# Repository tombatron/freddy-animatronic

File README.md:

# Freddy Animatronic: custom controller

Reverse-engineering the control board of a Spirit Halloween Freddy Fazbear animatronic, so it can be replaced with an ESP32-S3 that runs custom reactions (and later, sound and AI).

**Status (November 2026):** Phase 1 (listen and decode) is complete. Every motor, sensor and protocol is understood, and the ESP32 already drives both elbows directly. Phase 2 (a custom, drop-in controller board) is under way: the [rev A PCB](docs/phase2-pcb.md) (with a speaker amp) is laid out in KiCad, routed and ready to order, with a 3D-printable enclosure. Modules are in hand, and two bench tests are ready to run: the [power test](docs/phase2-power-test.md) and the [head test](docs/head-bench-test.md).

| Part | What it is | Status |
| --- | --- | --- |
| Shoulders | Reversing DC motor (~2 Ω) + one position switch | Decoded, both arms |
| Elbows | Smart serial servo module, 9600 baud, custom frames | Decoded **and controlled** by the ESP32 |
| Eyes | Sweep motor (cam disc), home switch, LEDs | Decoded; LED and motor currents measured |
| Trigger | 3.5mm jack, contact closure | Confirmed |
| PIR motion sensor | 3-wire sensor | Measured: yellow = ~7V power, orange = signal (~1.3V on motion) |

## System overview

```mermaid
flowchart LR
    PSU["7.2V 4A adapter"] --> PB["Power breakout<br/>5A fuse + GND tap"]
    PB --> SB["Stock board SD03-122<br/>(FMD FT60E122 MCU)"]
    SB -- "cable 1: H-bridge" --> SH["Shoulder motors x2"]
    SB -- "cable 3: 3.3V, GND, switch" --> SS["Shoulder switches x2"]
    SB -- "cable 2: 7V, GND, 9600 serial" --> EL["Elbow servo modules x2"]
    SB -- "head 3: switched" --> EM["Eye sweep motor"]
    SB -- "head 1: pull-up" --> EH["Eye home switch"]
    SB -- "head 2: switched" --> LED["Eye LEDs"]
    PIR["PIR sensor"] --> SB
    TRIG["Trigger jack"] --> SB
```

In Phase 2 the stock board is removed and an ESP32-S3 controller plugs into the same connectors.

## Repository layout

| Path | Contents |
| --- | --- |
| [docs/hardware-map.md](docs/hardware-map.md) | Every cable and wire, with its role and measured voltages |
| [docs/arms.md](docs/arms.md) | Shoulder drive, shoulder switch, elbow overview, measured ranges |
| [docs/elbow-protocol.md](docs/elbow-protocol.md) | The elbow serial protocol and checksum, and how it was cracked |
| [docs/head.md](docs/head.md) | Eye motor, home switch and LEDs |
| [docs/phase1-harness.md](docs/phase1-harness.md) | How the listening harness, tap boards and test rigs are built |
| [docs/tooling.md](docs/tooling.md) | Arduino IDE, picocom, PulseView/sigrok setup (Arch Linux and Windows) |
| [docs/troubleshooting.md](docs/troubleshooting.md) | Lessons learned the hard way |
| [docs/phase2-plan.md](docs/phase2-plan.md) | Requirements and parts for the custom controller |
| [docs/head-bench-test.md](docs/head-bench-test.md) | Head bench test: what else can the eyes do (speed, reverse, aim, glances, LED effects)? |
| [docs/phase2-power-test.md](docs/phase2-power-test.md) | Breadboard power test: does the 5V rail survive a shoulder lift? |
| [docs/phase2-pcb.md](docs/phase2-pcb.md) | Controller PCB rev A: KiCad project, GPIO map, connectors, power budget, ordering, enclosure |
| [docs/future-improvements.md](docs/future-improvements.md) | Later upgrades: eye angle sensor (AS5600 on the eye pivot), stock-compatible eye switch replacement, servo-driven eyes + radar tracking |
| [hardware/controller/](hardware/controller/) | KiCad project, fab files for JLCPCB, renders, enclosure, BOM, net list |
| [schematics/](schematics/) | Phase 1 SVG schematics (`tools/make_schematics.py`) and the controller schematic exported from KiCad |
| [firmware/](firmware/) | ESP32-S3 Arduino sketches (loggers, sniffer, elbow controllers) |
| [tools/](tools/) | `elbow_frame.py` (build and check frames), schematic generators, `kicad/` (generates the controller's KiCad project and enclosure from `design.py`) |
| [captures/](captures/) | Raw logs from the stock board, used for the analysis |

## Quick start: move an elbow

1. Build the elbow replay rig ([docs/phase1-harness.md](docs/phase1-harness.md#elbow-replay-rig)), with the stock board disconnected.
2. Flash [`firmware/freddy_elbow_controller`](firmware/freddy_elbow_controller/) to an ESP32-S3.
3. `picocom -b 115200 /dev/ttyACM0`, press `h` to home, then use the arrow keys to jog.

Or build any frame by hand:

```bash
python3 tools/elbow_frame.py build -400 1500
# AB 01 09 41 70 FE DC 05 45
```

## Safety notes

- Every ESP32 input goes through a 47k/22k divider (7.6V becomes 2.4V) or a 1kΩ series resistor. Nothing on the harness is wired straight to a GPIO.
- **Always tie the ESP32's ground to Freddy's ground.** A missing ground caused most of the confusing readings during Phase 1.
- Elbow commands are clamped to the measured ranges (right −700..350, left −700..550).

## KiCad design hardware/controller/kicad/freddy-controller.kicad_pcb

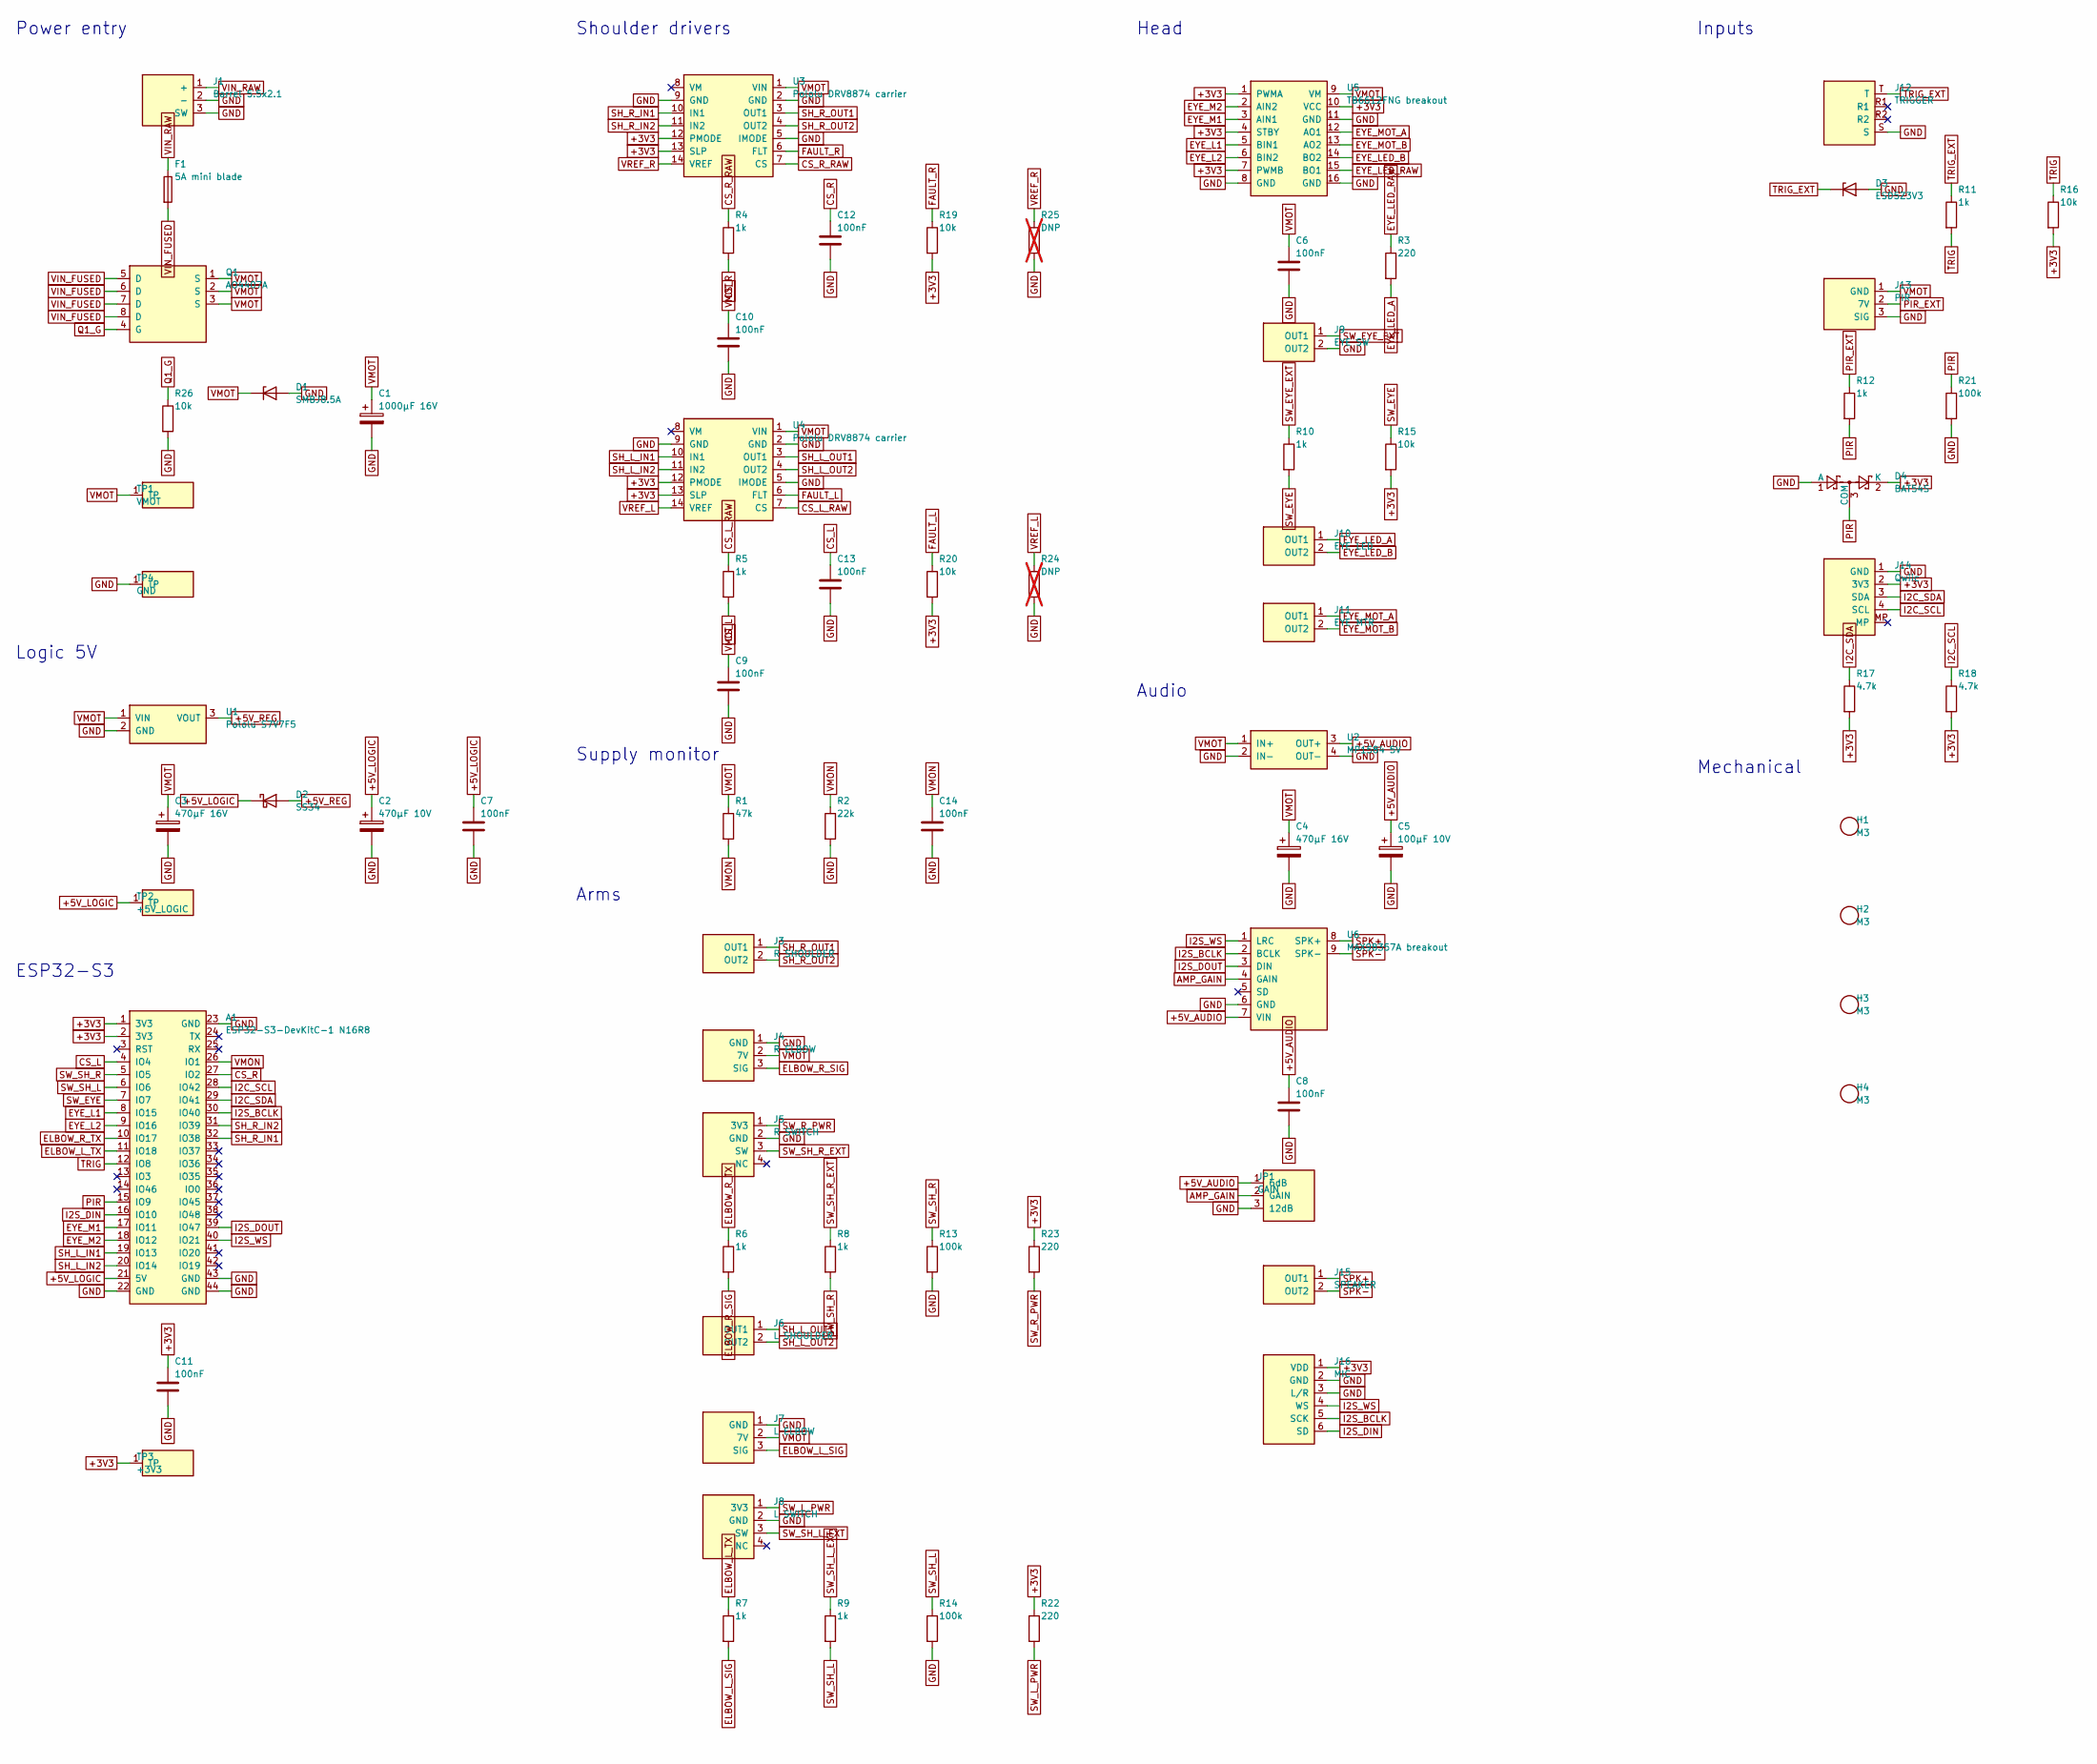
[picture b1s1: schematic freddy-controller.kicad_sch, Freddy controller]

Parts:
A1: ESP32-S3-DevKitC-1 N16R8; ESP32-S3-DevKitC-1_Socket; MPN YD-ESP32-S3 / DevKitC-1 (in hand)
C1: 1000µF 16V; CP_Radial_D10.0mm_P5.00mm; MPN 1000µF 16V low-ESR, 10mm
C2: 470µF 10V; CP_Radial_D6.3mm_P2.50mm; MPN 470µF 10V, 6.3mm
C3, C4: 470µF 16V; CP_Radial_D8.0mm_P3.50mm; MPN 470µF 16V, 8mm
C5: 100µF 10V; CP_Radial_D5.0mm_P2.00mm; MPN 100µF 10V, 5mm
C6, C7, C8, C9, C10, C11, C12, C13, C14: 100nF; C_0805_2012Metric
D1: SMBJ8.5A; D_SMB; MPN SMBJ8.5A (unidirectional TVS)
D2: SS34; D_SMA; MPN SS34
D3: ESD5Z3V3; D_SOD-523; MPN ESD5Z3V3
D4: BAT54S; SOT-23; MPN BAT54S
F1: 5A mini blade; Fuseholder_Blade_Mini_Keystone_3568; MPN Keystone 3568 + 5A mini blade fuse
H1, H2, H3, H4: M3; MountingHole_3.2mm_M3
J1: Barrel 5.5x2.1; BarrelJack_Horizontal; MPN 5.5x2.1mm PCB barrel jack, 5A+, CUI PJ-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
J3: R SHOULDER; Pigtail_1x2_P2.54mm_ZipTie; MPN JST SM 2-pin pigtail (in hand)
J4: R ELBOW; Pigtail_1x3_P2.54mm_ZipTie; MPN JST SM 3-pin pigtail (in hand)
J5: R SWITCH; Pigtail_1x4_P2.54mm_ZipTie; MPN JST SM 4-pin pigtail (in hand)
J6: L SHOULDER; Pigtail_1x2_P2.54mm_ZipTie; MPN JST SM 2-pin pigtail (in hand)
J7: L ELBOW; Pigtail_1x3_P2.54mm_ZipTie; MPN JST SM 3-pin pigtail (in hand)
J8: L SWITCH; Pigtail_1x4_P2.54mm_ZipTie; MPN JST SM 4-pin pigtail (in hand)
J9: EYE SW; Pigtail_1x2_P2.54mm_ZipTie; MPN JST SM 2-pin pigtail (in hand)
J10: EYE LED; Pigtail_1x2_P2.54mm_ZipTie; MPN JST SM 2-pin pigtail (in hand)
J11: EYE MTR; Pigtail_1x2_P2.54mm_ZipTie; MPN JST SM 2-pin pigtail (in hand)
J12: TRIGGER; Jack_3.5mm_KoreanHropartsElec_PJ-320D-4A_Horizontal; MPN PJ-320D 3.5mm jack
J13: PIR; Pigtail_1x3_P2.54mm_ZipTie; MPN JST SM 3-pin pigtail (in hand)
J14: Qwiic; JST_SH_SM04B-SRSS-TB_1x04-1MP_P1.00mm_Horizontal; MPN JST SM04B-SRSS-TB
J15: SPEAKER; Pigtail_1x2_P2.54mm_ZipTie; MPN solder pads: speaker wires straight in
J16: MIC; PinSocket_1x06_P2.54mm_Vertical; MPN 1x6 female header (INMP441, later)
JP1: GAIN; PinHeader_1x03_P2.54mm_Vertical; MPN 1x3 pin header + jumper
Q1: AO4407A; SOIC-8_3.9x4.9mm_P1.27mm; MPN AO4407A
R1: 47k; R_0805_2012Metric
R2: 22k; R_0805_2012Metric
R3: 220; R_1206_3216Metric
R4, R5, R6, R7, R8, R9, R10, R11, R12: 1k; R_0805_2012Metric
R13, R14, R21: 100k; R_0805_2012Metric
R15, R16, R19, R20, R26: 10k; R_0805_2012Metric
R17, R18: 4.7k; R_0805_2012Metric
R22, R23: 220; R_0805_2012Metric
R24, R25: DNP; R_0805_2012Metric; not fitted
TP1: VMOT; TestPoint_Pad_D1.5mm
TP2: +5V_LOGIC; TestPoint_Pad_D1.5mm
TP3: +3V3; TestPoint_Pad_D1.5mm
TP4: GND; TestPoint_Pad_D1.5mm
U1: Pololu S7V7F5; Pololu_S7V7F5_Upright; MPN Pololu #2119 (in hand)
U2: MP1584 5V; MP1584_Module; MPN MP1584EN fixed 5V module (in hand)
U3, U4: Pololu DRV8874 carrier; Pololu_DRV8874_Carrier_Socket; MPN Pololu #4035 (in hand)
U5: TB6612FNG breakout; TB6612FNG_Clone_ChipUp_Socket; MPN red TB6612FNG clone, labels on bottom, 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
U6: MAX98357A breakout; MAX98357A_Breakout_Socket; MPN Adafruit-style MAX98357A (in hand)

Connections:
+3V3: A1.1 (3V3), A1.2 (3V3), C11.1, D4.2 (K), J14.2 (3V3), J16.1 (VDD), R15.2, R16.2, R17.2, R18.2, R19.2, R20.2, R22.1, R23.1, TP3.1, U3.12 (PMODE), U3.13 (SLP), U4.12 (PMODE), U4.13 (SLP), U5.1 (PWMA), U5.4 (STBY), U5.7 (PWMB), U5.10 (VCC)
+5V_AUDIO: C5.1, C8.1, JP1.1 (6dB), U2.3 (OUT+), U6.7 (VIN)
+5V_LOGIC: A1.21 (5V), C2.1, C7.1, D2.1 (K), TP2.1
+5V_REG: D2.2 (A), U1.3 (VOUT)
AMP_GAIN: JP1.2 (GAIN), U6.4 (GAIN)
CS_L: A1.4 (IO4), C13.1, R5.2
CS_L_RAW: R5.1, U4.7 (CS)
CS_R: A1.27 (IO2), C12.1, R4.2
CS_R_RAW: R4.1, U3.7 (CS)
ELBOW_L_SIG: J7.3 (SIG), R7.2
ELBOW_L_TX: A1.11 (IO18), R7.1
ELBOW_R_SIG: J4.3 (SIG), R6.2
ELBOW_R_TX: A1.10 (IO17), R6.1
EYE_L1: A1.8 (IO15), U5.5 (BIN1)
EYE_L2: A1.9 (IO16), U5.6 (BIN2)
EYE_LED_A: J10.1 (OUT1), R3.2
EYE_LED_B: J10.2 (OUT2), U5.14 (BO2)
EYE_LED_RAW: R3.1, U5.15 (BO1)
EYE_M1: A1.17 (IO11), U5.3 (AIN1)
EYE_M2: A1.18 (IO12), U5.2 (AIN2)
EYE_MOT_A: J11.1 (OUT1), U5.12 (AO1)
EYE_MOT_B: J11.2 (OUT2), U5.13 (AO2)
FAULT_L: R20.1, U4.6 (FLT)
FAULT_R: R19.1, U3.6 (FLT)
GND: A1.22 (GND), A1.23 (GND), A1.43 (GND), A1.44 (GND), C1.2, C2.2, C3.2, C4.2, C5.2, C6.2, C7.2, C8.2, C9.2, C10.2, C11.2, C12.2, C13.2, C14.2, D1.2 (A), D3.2 (A), D4.1 (A), J1.2 (-), J1.3 (SW), J4.1 (GND), J5.2 (GND), J7.1 (GND), J8.2 (GND), J9.2 (OUT2), J12.S, J13.3 (SIG), J14.1 (GND), J16.2 (GND), J16.3 (L/R), JP1.3 (12dB), R2.2, R13.2, R14.2, R21.2, R24.2, R25.2, R26.2, TP4.1, U1.2 (GND), U2.2 (IN-), U2.4 (OUT-), U3.2 (GND), U3.5 (IMODE), U3.9 (GND), U4.2 (GND), U4.5 (IMODE), U4.9 (GND), U5.8 (GND), U5.11 (GND), U5.16 (GND), U6.6 (GND)
I2C_SCL: A1.28 (IO42), J14.4 (SCL), R18.1
I2C_SDA: A1.29 (IO41), J14.3 (SDA), R17.1
I2S_BCLK: A1.30 (IO40), J16.5 (SCK), U6.2 (BCLK)
I2S_DIN: A1.16 (IO10), J16.6 (SD)
I2S_DOUT: A1.39 (IO47), U6.3 (DIN)
I2S_WS: A1.40 (IO21), J16.4 (WS), U6.1 (LRC)
PIR: A1.15 (IO9), D4.3 (COM), R12.2, R21.1
PIR_EXT: J13.2 (7V), R12.1
Q1_G: Q1.4 (G), R26.1
SH_L_IN1: A1.19 (IO13), U4.10 (IN1)
SH_L_IN2: A1.20 (IO14), U4.11 (IN2)
SH_L_OUT1: J6.1 (OUT1), U4.3 (OUT1)
SH_L_OUT2: J6.2 (OUT2), U4.4 (OUT2)
SH_R_IN1: A1.32 (IO38), U3.10 (IN1)
SH_R_IN2: A1.31 (IO39), U3.11 (IN2)
SH_R_OUT1: J3.1 (OUT1), U3.3 (OUT1)
SH_R_OUT2: J3.2 (OUT2), U3.4 (OUT2)
SPK+: J15.1 (OUT1), U6.8 (SPK+)
SPK-: J15.2 (OUT2), U6.9 (SPK-)
SW_EYE: A1.7 (IO7), R10.2, R15.1
SW_EYE_EXT: J9.1 (OUT1), R10.1
SW_L_PWR: J8.1 (3V3), R22.2
SW_R_PWR: J5.1 (3V3), R23.2
SW_SH_L: A1.6 (IO6), R9.2, R14.1
SW_SH_L_EXT: J8.3 (SW), R9.1
SW_SH_R: A1.5 (IO5), R8.2, R13.1
SW_SH_R_EXT: J5.3 (SW), R8.1
TRIG: A1.12 (IO8), R11.2, R16.1
TRIG_EXT: D3.1 (K), J12.T, R11.1
VIN_FUSED: F1.2, Q1.5 (D), Q1.6 (D), Q1.7 (D), Q1.8 (D)
VIN_RAW: F1.1, J1.1 (+)
VMON: A1.26 (IO1), C14.1, R1.2, R2.1
VMOT: C1.1, C3.1, C4.1, C6.1, C9.1, C10.1, D1.1 (K), J4.2 (7V), J7.2 (7V), J13.1 (GND), Q1.1 (S), Q1.2 (S), Q1.3 (S), R1.1, TP1.1, U1.1 (VIN), U2.1 (IN+), U3.1 (VIN), U4.1 (VIN), U5.9 (VM)
VREF_L: R24.1, U4.14 (VREF)
VREF_R: R25.1, U3.14 (VREF)

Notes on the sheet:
Power entry
Logic 5V
ESP32-S3
Shoulder drivers
Supply monitor
Arms
Head
Audio
Inputs
Mechanical

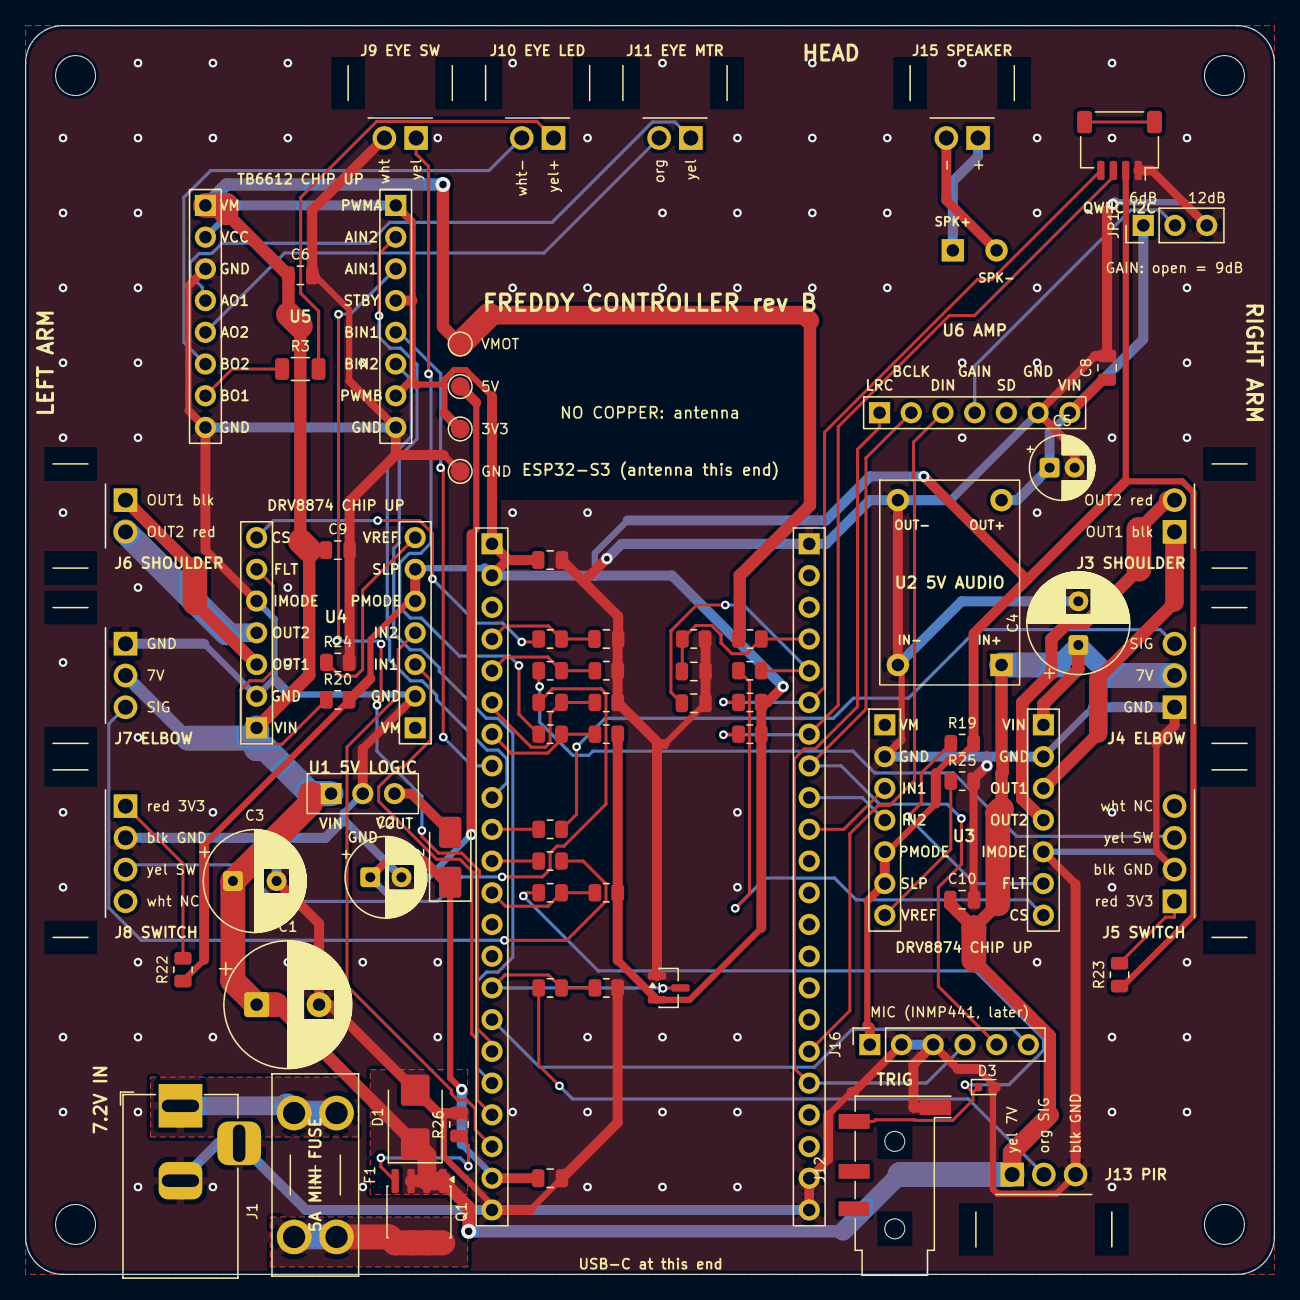
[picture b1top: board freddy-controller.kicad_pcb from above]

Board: 2 copper layers, 100.0 x 100.0 mm, 77 parts (0 on the bottom side), 60 nets.

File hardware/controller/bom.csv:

Refs,Qty,Value,Part / MPN,Footprint,Fitting
A1,1,ESP32-S3-DevKitC-1 N16R8,YD-ESP32-S3 / DevKitC-1 (in hand),Freddy:ESP32-S3-DevKitC-1_Socket,hand-solder
C1,1,1000µF 16V,"1000µF 16V low-ESR, 10mm",Capacitor_THT:CP_Radial_D10.0mm_P5.00mm,hand-solder
C2,1,470µF 10V,"470µF 10V, 6.3mm",Capacitor_THT:CP_Radial_D6.3mm_P2.50mm,hand-solder
C3 C4,2,470µF 16V,"470µF 16V, 8mm",Capacitor_THT:CP_Radial_D8.0mm_P3.50mm,hand-solder
C5,1,100µF 10V,"100µF 10V, 5mm",Capacitor_THT:CP_Radial_D5.0mm_P2.00mm,hand-solder
C6 C7 C8 C9 C10 C11 C12 C13 C14,9,100nF,,Capacitor_SMD:C_0805_2012Metric,JLC assembly (SMD)
D1,1,SMBJ8.5A,SMBJ8.5A (unidirectional TVS),Diode_SMD:D_SMB,JLC assembly (SMD)
D2,1,SS34,SS34,Diode_SMD:D_SMA,JLC assembly (SMD)
D3,1,ESD5Z3V3,ESD5Z3V3,Diode_SMD:D_SOD-523,JLC assembly (SMD)
D4,1,BAT54S,BAT54S,Package_TO_SOT_SMD:SOT-23,JLC assembly (SMD)
F1,1,5A mini blade,Keystone 3568 + 5A mini blade fuse,Fuse:Fuseholder_Blade_Mini_Keystone_3568,hand-solder
J1,1,Barrel 5.5x2.1,"5.5x2.1mm PCB barrel jack, 5A+, CUI PJ-002A-style pinout (check against the footprint)",Connector_BarrelJack:BarrelJack_Horizontal,hand-solder
J3,1,R SHOULDER,JST SM 2-pin pigtail (in hand),Freddy:Pigtail_1x2_P2.54mm_ZipTie,hand-solder
J4,1,R ELBOW,JST SM 3-pin pigtail (in hand),Freddy:Pigtail_1x3_P2.54mm_ZipTie,hand-solder
J5,1,R SWITCH,JST SM 4-pin pigtail (in hand),Freddy:Pigtail_1x4_P2.54mm_ZipTie,hand-solder
J6,1,L SHOULDER,JST SM 2-pin pigtail (in hand),Freddy:Pigtail_1x2_P2.54mm_ZipTie,hand-solder
J7,1,L ELBOW,JST SM 3-pin pigtail (in hand),Freddy:Pigtail_1x3_P2.54mm_ZipTie,hand-solder
J8,1,L SWITCH,JST SM 4-pin pigtail (in hand),Freddy:Pigtail_1x4_P2.54mm_ZipTie,hand-solder
J9,1,EYE SW,JST SM 2-pin pigtail (in hand),Freddy:Pigtail_1x2_P2.54mm_ZipTie,hand-solder
J10,1,EYE LED,JST SM 2-pin pigtail (in hand),Freddy:Pigtail_1x2_P2.54mm_ZipTie,hand-solder
J11,1,EYE MTR,JST SM 2-pin pigtail (in hand),Freddy:Pigtail_1x2_P2.54mm_ZipTie,hand-solder
J12,1,TRIGGER,PJ-320D 3.5mm jack,Connector_Audio:Jack_3.5mm_KoreanHropartsElec_PJ-320D-4A_Horizontal,JLC assembly (SMD)
J13,1,PIR,JST SM 3-pin pigtail (in hand),Freddy:Pigtail_1x3_P2.54mm_ZipTie,hand-solder
J14,1,Qwiic,JST SM04B-SRSS-TB,Connector_JST:JST_SH_SM04B-SRSS-TB_1x04-1MP_P1.00mm_Horizontal,JLC assembly (SMD)
J15,1,SPEAKER,solder pads: speaker wires straight in,Freddy:Pigtail_1x2_P2.54mm_ZipTie,hand-solder
J16,1,MIC,"1x6 female header (INMP441, later)",Connector_PinSocket_2.54mm:PinSocket_1x06_P2.54mm_Vertical,hand-solder
JP1,1,GAIN,1x3 pin header + jumper,Connector_PinHeader_2.54mm:PinHeader_1x03_P2.54mm_Vertical,hand-solder
Q1,1,AO4407A,AO4407A,Package_SO:SOIC-8_3.9x4.9mm_P1.27mm,JLC assembly (SMD)
R1,1,47k,,Resistor_SMD:R_0805_2012Metric,JLC assembly (SMD)
R2,1,22k,,Resistor_SMD:R_0805_2012Metric,JLC assembly (SMD)
R3,1,220,,Resistor_SMD:R_1206_3216Metric,JLC assembly (SMD)
R4 R5 R6 R7 R8 R9 R10 R11 R12,9,1k,,Resistor_SMD:R_0805_2012Metric,JLC assembly (SMD)
R13 R14 R21,3,100k,,Resistor_SMD:R_0805_2012Metric,JLC assembly (SMD)
R15 R16 R19 R20 R26,5,10k,,Resistor_SMD:R_0805_2012Metric,JLC assembly (SMD)
R17 R18,2,4.7k,,Resistor_SMD:R_0805_2012Metric,JLC assembly (SMD)
R22 R23,2,220,,Resistor_SMD:R_0805_2012Metric,JLC assembly (SMD)
R24 R25,2,DNP,,Resistor_SMD:R_0805_2012Metric,DNP
U1,1,Pololu S7V7F5,Pololu #2119 (in hand),Freddy:Pololu_S7V7F5_Upright,hand-solder
U2,1,MP1584 5V,MP1584EN fixed 5V module (in hand),Freddy:MP1584_Module,hand-solder
U3 U4,2,Pololu DRV8874 carrier,Pololu #4035 (in hand),Freddy:Pololu_DRV8874_Carrier_Socket,hand-solder
U5,1,TB6612FNG breakout,"red TB6612FNG clone, labels on bottom, chip up (in hand)",Freddy:TB6612FNG_Clone_ChipUp_Socket,hand-solder
U6,1,MAX98357A breakout,Adafruit-style MAX98357A (in hand),Freddy:MAX98357A_Breakout_Socket,hand-solder
sockets,2,1x22 female header 2.54mm,A1 ESP32 (rows 25.4mm apart),,hand-solder
sockets,4,1x7 female header 2.54mm,"U3/U4 DRV8874, round-pin preferred (~3A pins)",,hand-solder
sockets,2,1x8 female header 2.54mm,U5 TB6612,,hand-solder
sockets,1,1x7 female header 2.54mm,U6 amp,,hand-solder
sockets,1,1x3 female header 2.54mm,U1 S7V7F5 (upright),,hand-solder
sockets,6,single-pin machined socket,U2 MP1584 corners (4) or solder flat; U6 speaker holes (2),,hand-solder
-,1,male header pins,for each module (Pololu boards ship with loose headers),,hand-solder
-,1,jumper cap 2.54mm,JP1 (optional: open = 9dB),,hand-solder
enclosure,4,"M3x20 screw (self-tapping, or with heat-set inserts)",base -> PCB -> lid posts,,assembly

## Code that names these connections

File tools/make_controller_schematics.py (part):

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    d += elm.Line().right(1.6)
    d += (vm := elm.Dot())
    d += elm.Line().right(4.2)
    d += elm.Dot(open=True).label("VMOT", "right")
    d += elm.Capacitor(polar=True).at(vm.center).down().label("C1 1000µF 16V", "bottom", fontsize=10)
    d += elm.Ground()
    d += elm.Zener().at((vm.center[0] + 3.0, vm.center[1])).down().reverse().label("D1 TVS\nSMBJ8.5A", "bottom", fontsize=10)
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
    # supply monitor
    d += elm.Label().label("Supply monitor", fontsize=12, halign="left").at((16, 6.9))
    d += elm.Dot(open=True).at((16, 6)).label("VMOT", "left")
    d += elm.Resistor().right().label("R1 47k")
    d += (mj := elm.Dot())
    d += elm.Line().right(0.8)
    d += elm.Dot(open=True).label("VMON → GPIO1", "right")
    d += elm.Resistor().at(mj.center).down().label("R2 22k", "bottom")
    d += elm.Ground()

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    d += elm.Label().label("Pololu #4035 (2×7, rows 0.5\"). Onboard 2.49k on CS: 450µA/A × 2.49k = 1.12V/A; limit = VREF ÷ 1.12 = ≈2.9A at 3.3V. Power into VIN, not VM.", fontsize=10, halign="left", color="#555").at((0, -1.2))
    module(d, "U5 TB6612FNG · eye motor (A) + eye LEDs (B)",
           [("VM", "VMOT"), ("VCC", "+3V3"), ("GND", "GND"), ("STBY", "+3V3"), ("PWMA", "+3V3"), ("PWMB", "+3V3"),
            ("AIN1", "EYE_M1 (GPIO38)"), ("AIN2", "EYE_M2 (GPIO39)"), ("BIN1", "EYE_L1 (GPIO41)"), ("BIN2", "EYE_L2 (GPIO42)")],
           [("AO1", "J11.1 eye motor (yellow)"), ("AO2", "J11.2 eye motor (orange)"),
            ("BO1", "R3 220Ω → J10.1 LED + (yellow)"), ("BO2", "J10.2 LED − (white)")],
           (10, -12), width=3.6)
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        d.add(elm.Resistor().right().label("1k"))
        d.add(elm.Line().right(1))
        d.add(elm.Dot(open=True).label(f"{j}.3 signal (row 5)", "right"))
        d.add(elm.Dot(open=True).at((5.2, y - 0.8)).label(f"{j}.2 power (row 4) = VMOT", "right"))
        d.add(elm.Dot(open=True).at((5.2, y - 1.5)).label(f"{j}.1 GND (row 3)", "right"))

    elbow(10, "R", "GPIO17 · UART1", "J4")
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            d.add(elm.Resistor().at(n.center).down().label(pull, "bottom"))
            d.add(elm.Dot(open=True).label("+3V3", "bottom"))

    switch_in(16, 10, "Right shoulder switch · J5", "J5.3 yellow", "SW_SH_R (GPIO5)", "100k", "GND")
    switch_in(16, 4.8, "Left shoulder switch · J8", "J8.3 yellow", "SW_SH_L (GPIO6)", "100k", "GND")
    d += elm.Label().label("J5/J8: pin 1 = +3V3 via 220Ω (R22/R23, red), 2 = GND, 3 = switch (yellow), 4 = white → TP", fontsize=10, halign="left", color="#555").at((16, 0.6))

    switch_in(0, 2.5, "Eye home switch · J9 (head cable 1)", "J9.1 yellow", "SW_EYE (GPIO7)", "10k", "3V3")
    d += elm.Label().label("J9.2 white = GND", fontsize=10, halign="left", color="#555").at((0, -1.5))
    switch_in(16, -1.4, "Trigger · J12 (3.5mm mono)", "J12 tip", "TRIG (GPIO8)", "10k", "3V3")
    d += elm.Label().label("J12 sleeve = GND; TVS (ESD5Z3V3) tip to GND", fontsize=10, halign="left", color="#555").at((16, -5.6))

    d += elm.Label().label("PIR · J13", fontsize=12, halign="left").at((0, -3))
    d += elm.Dot(open=True).at((0, -4)).label("J13.2 orange (signal)", "left")
    d += elm.Resistor().right().label("1k")
    d += elm.Line().right(1)
    d += elm.Dot(open=True).label("PIR (GPIO9, ADC) + 100k to GND + BAT54S clamp", "right")
    d += elm.Label().label("J13.1 = VMOT (yellow, power), J13.3 = GND (black). Output is ~1.3V on motion: read it with the ADC, threshold ~0.6V.", fontsize=10, halign="left", color="#555").at((0, -5))

    d += elm.Label().label("I2C · J14 (JST-SH 4-pin, Qwiic/STEMMA QT)", fontsize=12, halign="left").at((16, -6.8))
    d += elm.Label().label("GND, +3V3, SDA = GPIO15, SCL = GPIO16; 4.7k pull-ups to 3V3.\nFor INA219 (current) and MPU6050 (shoulder angle).", fontsize=10, halign="left").at((16, -8))
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with drawing("controller_audio.svg") as d:
    title(d, "Controller rev A · sheet 4: audio", "One I2S bus, full duplex: amplifier out, optional microphone in", (0, 7))
    module(d, "U6 MAX98357A I2S amp module (3W, class D)",
           [("VIN", "+5V_AUDIO"), ("GND", "GND"), ("BCLK", "I2S_BCLK (GPIO40)"), ("LRC", "I2S_WS (GPIO21)"),
            ("DIN", "I2S_DOUT (GPIO47)"), ("GAIN", "JP1: open 9dB / GND 12dB / VIN 6dB"), ("SD", None)],
           [("SPK+", "J15.1 speaker + (pad)"), ("SPK−", "J15.2 speaker − (pad)")], (3, -1), width=3.4)
    module(d, "J16 microphone header (INMP441 module)",
           [("VDD", "+3V3"), ("GND", "GND"), ("SCK", "I2S_BCLK (GPIO40)"), ("WS", "I2S_WS (GPIO21)"),
            ("SD", "I2S_DIN (GPIO10)"), ("L/R", "GND (left)")], [], (20, -1), width=2.6)
    d += elm.Label().label("Speaker: 4–8Ω, up to ~3W. Keep the amp and speaker leads away from the motor drivers.", fontsize=10, halign="left", color="#555").at((0, -6.8))

# ---------------------------------------------------------------- esp32
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    title(d, "Controller rev A · sheet 5: ESP32-S3 dev board", "Plugs into 2×22 female headers. Avoids strapping pins (0, 3, 45, 46), USB (19, 20), PSRAM (35–37) and UART0 (43, 44)", (0, 14.6))
    module(d, "ESP32-S3 DevKitC-1 style (N16R8)",
           [("5V", "+5V_LOGIC (via D2)"), ("3V3", "+3V3 (out, sensors/logic)"), ("GND", "GND"),
            ("GPIO1", "VMON"), ("GPIO2", "CS_R"), ("GPIO4", "CS_L"), ("GPIO5", "SW_SH_R"), ("GPIO6", "SW_SH_L"),
            ("GPIO7", "SW_EYE"), ("GPIO8", "TRIG"), ("GPIO9", "PIR"), ("GPIO10", "I2S_DIN (mic)"),
            ("GPIO11", "SH_R_IN1"), ("GPIO12", "SH_R_IN2")],
           [("GPIO13", "SH_L_IN1"), ("GPIO14", "SH_L_IN2"), ("GPIO15", "I2C_SDA"), ("GPIO16", "I2C_SCL"),
            ("GPIO17", "ELBOW_R_TX"), ("GPIO18", "ELBOW_L_TX"), ("GPIO21", "I2S_WS"), ("GPIO38", "EYE_M1"),
            ("GPIO39", "EYE_M2"), ("GPIO40", "I2S_BCLK"), ("GPIO41", "EYE_L1"), ("GPIO42", "EYE_L2"),
            ("GPIO47", "I2S_DOUT (amp)"), ("GPIO48", "onboard RGB LED")],
           (6, 0), width=5)

# ---------------------------------------------------------------- placement (to scale, mm)
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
